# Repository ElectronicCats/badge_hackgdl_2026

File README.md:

# Badge Hack GDL 2026

El Badge Hack GDL 2026 es un dispositivo de hardware abierto diseñado para la
comunidad de hackers, desarrolladores y entusiastas de la tecnología. Integra
un procesador Linux RV1106 con cámara, LED RGB, botones y USB-C, y un firmware
propio con captura de fotos, MTP, ADB y un editor visual de overlay.

## 🚀 Características Principales

### Procesador principal

- **RV1106G3**: procesador Linux de alto rendimiento
  - ARM Cortex-A7 + MCU RISC-V
  - NPU integrada
  - ISP integrado
  - Soporte completo para Linux

### Interfaces y Conectividad

- **GPIOs**: pines de propósito general
- **MIPI CSI**: cámara SC3336 de 3 MP
- **UART**: consola serial de depuración
- **USB-C**: datos y alimentación (MTP, ADB y RNDIS)

### Periféricos Integrados

- **NeoPixel**: LED RGB WS2812E por SPI
- **Batería**: soporte para 18650 con gestión de energía
- **Buck Converter**: regulación DC-DC
- **Cámara**: SC3336, 2304×1296
- **Botones**: 5 botones `gpio-keys`

## 📦 Componentes del Proyecto

El proyecto está dividido en tres bloques:

### 1. Badge Principal (`hardware/`)

Incluye el diseño principal:

- Procesador RV1106G3
- LED NeoPixel WS2812E
- Gestión de energía y batería
- Interfaz MIPI para la cámara
- USB-C y botones

### 2. Firmware (`luckfox-pico`)

La capa de firmware vive en la rama `badge_hackgdl_2026_v2` del
repositorio [`ElectronicCats/luckfox-pico`](https://github.com/ElectronicCats/luckfox-pico).
Incluye:

- `badge_photo`: captura, AIQ/ISP, overlay, motor RGB y botones;
- `overlay_web`: editor visual y streaming MJPEG;
- `rndis_dhcp`: red USB y DHCP;
- MTP/ADB sobre FunctionFS con uMTP-Responder;
- board config, DTS, kernel fragment, MCU y overlay;
- scripts de build, flasheo y pruebas.

### 3. Add-ons (`Add-ons/`)

Diseños y firmware de los add-ons Pescadito y Tortuguita.

## 📋 Especificaciones Técnicas

| Componente | Especificación |
|---|---|
| Procesador | RV1106G3 (ARM Cortex-A7 + RISC-V MCU + NPU + ISP) |
| Sistema Operativo | Linux (BusyBox) |
| Cámara | SC3336, 2304×1296, MIPI CSI-2 |
| LED | WS2812E NeoPixel por SPI0 |
| Batería | 18650 |
| USB | USB-C: MTP + ADB + RNDIS |
| Botones | 5 `gpio-keys` |
| Almacenamiento | SPI NAND 256 MB, `/userdata` UBIFS |

## 🔌 Interfaces del RV1106

### Comunicación

- **UART**: consola serial de depuración
- **SPI**: LED WS2812 y periféricos
- **I2C**: cámara y sensores
- **USB**: MTP, ADB y RNDIS

### Multimedia e Imagen

- **MIPI CSI**: cámara SC3336
- **ISP**: procesamiento de imagen integrado
- **VENC**: JPEG y MJPEG para fotos y editor

### Control

- **GPIOs**: botones, LED y señales de la cámara
- **PWM**: disponible para periféricos

---

## **Primeros pasos**

El badge está basado en el hardware y el SDK de la Luckfox Pico Pro Max. Para
detalles de la plataforma puedes consultar la
[Wiki oficial de Luckfox](https://wiki.luckfox.com/Luckfox-Pico-Pro-Max/).

En esta sección aprenderás a:

- encender y usar tu badge;
- tomar fotografías;
- copiar las imágenes a tu computadora;
- personalizar el overlay de las fotos;
- abrir el editor web.

### **1. Alimentar tu badge**

Puedes alimentar la badge de dos maneras:

- con una batería **18650** en el compartimento trasero;
- por **USB-C** desde una computadora o cargador.

Respeta la polaridad marcada en el portapilas. El USB-C también transporta
MTP, ADB y RNDIS.

### **2. Encender el badge**

El interruptor **OFF/ON** está en el lado derecho de la placa.

1. Conecta la batería y/o el USB-C.
2. Coloca el interruptor en **ON**.
3. Espera el **doble destello verde** del NeoPixel.

El arranque es **cámara-first**: la aplicación inicia la cámara y el LED, y
sólo cuando la cámara está lista expone MTP, ADB y la web. En el arranque real
esto tarda aproximadamente **25–30 segundos**. Es normal que durante ese tiempo
la badge todavía no aparezca en la computadora.

### **3. Botones**

| Botón | `gpio-keys` | Función por defecto |
|---|---|---|
| Superior | `KEY_ENTER` | Tomar foto |
| USER1 (arriba) | `KEY_UP` | Acción de usuario programable |
| USER2 | `KEY_RIGHT` | Acción de usuario programable |
| USER3 | `KEY_LEFT` | Siguiente rutina RGB |
| USER4 (abajo) | `KEY_DOWN` | Rutina RGB anterior |

USER1 y USER2 están libres para que agregues tus propias acciones en
`badge/app/src/user_led.c`.

### **Blink Blink!**

Presiona **USER3** y **USER4** para recorrer las rutinas del NeoPixel:

1. `Off`
2. `Breath`
3. `Rainbow`
4. `Pulse`
5. `Alert`
6. `Candle`

Al arrancar, el LED hace dos destellos verdes y luego queda en `Off` hasta que
selecciones una rutina.

### **📸 Tomar fotografías**

Con la badge encendida y la cámara lista, presiona el **botón superior**.

Al capturar:

- el NeoPixel hace un destello blanco;
- la foto se guarda en `/userdata/photos`;
- el JPEG aparece por MTP en **Badge Hack GDL 2026 Photos**.

La foto final es de **2304×1296**, con giro de 180° y el overlay configurado.
El nombre usa la fecha y hora del sistema; como la badge no tiene RTC con
batería, es normal ver nombres como `IMG_19700101_000611_0000.jpg`.

### **💾 Extraer fotografías**

Las imágenes se transfieren por **MTP**. Conecta la badge por USB-C y espera a
que termine el arranque de la cámara.

**Windows**

1. Abre **Este equipo**.
2. Entra a **Badge Hack GDL 2026**.
3. Abre **Badge Hack GDL 2026 Photos**.
4. Copia los archivos `IMG_*.jpg`.
5. Usa **Quitar hardware de forma segura** antes de desconectar.

**Linux (GNOME/gvfs)**

1. Conecta la badge.
2. Abre el gestor de archivos; aparece como **Badge Hack GDL 2026**.
3. Entra a **Badge Hack GDL 2026 Photos**.

También puedes usar la terminal:

```bash
gio mount mtp://
gio list 'mtp://Electronic_Cats_Badge_Hack_GDL_2026_<serial>/Badge Hack GDL 2026 Photos'
```

**macOS:** instala **OpenMTP** o **Android File Transfer** y abre el
dispositivo. La carpeta de fotos tiene el mismo nombre.

La carpeta **Badge Config** contiene `overlay.ini`, la configuración del
overlay. Puedes copiarla, editarla en tu computadora y volver a copiarla; la
app y el editor la detectan automáticamente.

> En Windows, algunos clientes MTP no permiten editar un archivo “en sitio”.
> Si falla, copia `overlay.ini` al escritorio, edítalo y cópialo de vuelta a
> **Badge Config**. También puedes usar el editor web.

### **⚙ Archivo `overlay.ini`**

`overlay.ini` define el texto y los dos logos que se dibujan sobre la foto.
Ejemplo con los valores por defecto:

```ini
[logo1]
enabled = 1
x = 160
y = 1034
image = /oem/usr/share/badge/electroniccats.bmp

[logo2]
enabled = 1
x = 1976
y = 1024
image = /oem/usr/share/badge/hack_gdl.bmp

[text]
enabled = 1
x = 828
y = 92
text = Hack GDL 2026
size = 100
color = fff799
font = /oem/usr/share/badge/font.ttf
```

- `enabled`: `1` muestra el elemento, `0` lo oculta.
- `x`, `y`: posición en píxeles. El RGN del RV1106 exige coordenadas **pares**;
  la app y el editor las normalizan.
- `image`: ruta del BMP dentro de la imagen.
- `text`, `size`, `color`, `font`: texto, tamaño, color RGB hexadecimal y
  fuente del OSD.

Los cambios se aplican a la siguiente foto. Puedes editar el archivo por MTP o
usar el editor web; ambos escriben el mismo `overlay.ini`.

### **🖼 Editor web**

Con la badge conectada por USB, la computadora obtiene una interfaz de red USB
(RNDIS) con IP `192.168.42.2`. Abre:

```text
http://192.168.42.1/
```

El editor permite:

- arrastrar los dos logos y el texto sobre la vista de la cámara;
- cambiar texto, tamaño, color, visibilidad y posición X/Y;
- ver el stream MJPEG en vivo;
- capturar una foto con **Capturar foto**;
- editar `overlay.ini` sin botón de guardar: el autoguardado escribe el archivo;
- ver cambios hechos por MTP sin recargar la página (sincronización en ambos
  sentidos).

Si la página no abre, espera a que termine el arranque de la cámara y revisa
que el adaptador RNDIS tenga IP. Si no hay DHCP, asigna manualmente
`192.168.42.2/24`.

---

# **🚀 ¿Te interesa saber más sobre cómo se programó todo esto?**

El firmware se organiza en una capa limpia dentro de `luckfox-pico`:

- `badge/app/src/main.c`: arranque cámara-first, botones y ciclo principal;
- `badge/app/src/camera.c`: pipeline VI/VENC y captura JPEG;
- `badge/app/src/aiq.c`: carga de AIQ y calibración del ISP;
- `badge/app/src/overlay.c`: overlay RGN (logos y texto);
- `badge/app/src/led_engine.c` y `user_led.c`: motor y rutinas RGB;
- `badge/app/src/overlay_web.c`: servidor del editor y streaming;
- `badge/configs/overlay-badge-fastboot/etc/init.d/S49mtp`: gadget USB;
- `badge/scripts/`: build, flasheo y pruebas.

La documentación de build y flasheo está en el
[README de la capa](https://github.com/ElectronicCats/luckfox-pico/blob/badge_hackgdl_2026_v2/badge/README.md).

---

## 🔌 Conectarse al puerto serial (Debug Serial)

Para ver logs o depurar, conecta un adaptador USB-UART de **3.3 V** al puerto
DEBUG SERIAL. Corresponde a la UART2 del RV1106:

```text
TX del adaptador → RX del badge (GPIO1_B3)
RX del adaptador → TX del badge (GPIO1_B2)
GND → GND
```

> La señal es **3.3 V TTL**. No uses adaptadores de 5 V sin nivelador.

## ✔ Adaptadores USB–Serial compatibles

Puedes usar cualquier adaptador USB-UART de 3.3 V, por ejemplo:

- CH340 / CH341
- CP2102 / CP2104
- FT232RL
- PL2303
- CP2105
- Matek F405

## 💻 Cómo abrir la terminal serial

### 🐧 Linux

```bash
dmesg | grep tty
screen /dev/ttyUSB0 115200
# o:
sudo minicom -b 115200 -D /dev/ttyUSB0
```

Para salir de `screen`: `CTRL+A`, luego `K`.

### 🍎 macOS

```bash
ls /dev/tty.*
screen /dev/tty.usbserial-XXXX 115200
```

Para salir: `CTRL+A`, luego `K`. También puedes usar CoolTerm.

### 🪟 Windows

Usa PuTTY, TeraTerm, CoolTerm o RealTerm. En el Administrador de dispositivos
identifica el puerto COM y configura:

```text
Baudrate: 115200
Data bits: 8
Parity: None
Stop bits: 1
Flow control: None
```

---

### **Comunicación ADB**

ADB está habilitado en la imagen. Se expone después del arranque de la cámara
(~25–30 s).

1. Conecta la badge por USB-C.
2. Ejecuta:

```bash
adb devices
adb shell
```

El shell entra como **root**. ADB forma parte de las Android Platform Tools:

```text
https://developer.android.com/studio/releases/platform-tools
```

En Linux también puedes instalarlo con:

```bash
sudo apt update
sudo apt install android-tools-adb
```

---

## 🛠 Compilar el firmware

### Requisitos

- Linux x86_64 (probado en Ubuntu).
- Git, make, gcc/g++, bc, cpio, rsync, fakeroot, dtc, mkimage, python3, scons.
- ~25 GB libres para el SDK y los artefactos.
- Para flashear: `upgrade_tool` y acceso USB a la badge.

### Clonar y compilar

```bash
git clone -b badge_hackgdl_2026_v2 --single-branch \
  https://github.com/ElectronicCats/luckfox-pico.git
cd luckfox-pico
./badge/build.sh all
```

La primera compilación crea un worktree del SDK en `badge/build/luckfox-pico`,
descarga el toolchain RISC-V del HPMCU (~550 MB) y compila la imagen. Las
compilaciones siguientes reutilizan el worktree.

Si faltan `bison`, `flex`, `m4` o `python`, instálalos sin sudo:

```bash
./badge/scripts/install-host-tools.sh
```

Etapas disponibles:

```text
media, uboot, kernel, rootfs, app, pack, firmware, clean
```

Resultado:

```text
badge/out/update.img
```

El empaquetador de Rockchip incluye la hora de compilación en `update.img`, por
lo que un rebuild limpio no es byte-idéntico a la imagen de release. La imagen
validada de esta versión tiene:

```text
SHA256 21a1dc67597e43aa473b774031d7ca5f01394b59c68c1778c478361bb57895eb
```

La imagen validada se publicará en la sección **Releases** del repositorio; el
binario no se versiona en Git.

---

## 🌳 Device Tree y botones

La capa incluye el DTS `rv1106g-badge-fastboot.dts`; no necesitas editar el
árbol de Luckfox a mano. Los botones se exponen como `gpio-keys`:

| Botón | GPIO | Código Linux | Función |
|---|---|---|---|
| Superior | `GPIO1_D3` | `KEY_ENTER` | Captura |
| USER1 | `GPIO2_B1` | `KEY_UP` | Libre |
| USER2 | `GPIO2_B0` | `KEY_RIGHT` | Libre |
| USER3 | `GPIO2_A7` | `KEY_LEFT` | Siguiente rutina |
| USER4 | `GPIO2_A6` | `KEY_DOWN` | Rutina anterior |

El DTS también configura:

- cámara SC3336 en I2C4 (`0x30`) y MIPI CSI-2 de 2 lanes;
- LED WS2812 en SPI0 (`/dev/spidev0.0`);
- USB en modo `peripheral`;
- eliminación de `fbtft` y `mis5001` para evitar conflictos.

Puedes leer los eventos desde `/dev/input/eventX` en C o Python.

---

## 💡 NeoPixel y rutinas RGB

El motor está en `badge/app/src/led_engine.c`:

- no usa hilos, `sleep()` ni `malloc()`;
- llama a cada rutina cada ~20 ms;
- la rutina llena tres bytes (`R`, `G`, `B`) y regresa;
- el motor escribe el WS2812 por SPI a 2.4 MHz.

Para agregar una rutina, edita `badge/app/src/user_led.c`:

```c
static void my_routine(uint32_t elapsed_ms, uint8_t *rgb)
{
    uint8_t blink = ((elapsed_ms / 250) & 1) ? 255 : 0;

    rgb[0] = blink;      /* R */
    rgb[1] = 0;          /* G */
    rgb[2] = blink / 2;  /* B */
}

const led_pattern_t user_led_patterns[] = {
    { "USER demo", user_demo_frame },
    { "Mi rutina", my_routine },
};
```

USER3/USER4 recorren la lista; USER1/USER2 llaman a los hooks
`user_led_on_button_up()` y `user_led_on_button_right()`. No bloquees la rutina
ni escribas directamente en `/dev/spidev0.0`.

---

## 📸 Captura de fotografías

La captura la realiza `badge_photo`:

- inicia AIQ/ISP antes de abrir la cámara;
- espera un frame de warmup y reinicia el pipeline si hace falta;
- usa VENC 0 (JPEG q=90) para la foto final;
- usa VENC 1 (JPEG q=55, sin RGN) para el preview del editor;
- aplica giro de 180° y el overlay RGN;
- escribe el JPEG en `/userdata/.badge_photo_staging` y lo renombra a
  `/userdata/photos`.

El botón superior dispara la captura; el LED hace un destello blanco. La app
sigue viva si una captura falla y reintenta.

---

## 💾 MTP y configuración

`S49mtp` crea un gadget USB con:

- **MTP** por FunctionFS (`umtprd`);
- **ADB** por FunctionFS;
- **RNDIS** para la red USB.

El orden de arranque es:

```text
rcS → badge_photo → /tmp/badge_system.ready → S49mtp → MTP/ADB/RNDIS
```

MTP expone:

| Carpeta | Contenido |
|---|---|
| `Badge Hack GDL 2026 Photos` | Fotos `IMG_*.jpg` |
| `Badge Config` | `overlay.ini` |

No se expone `/userdata` completo ni el rootfs. El archivo `overlay.ini` se
publica en modo `0666` para que los clientes MTP puedan sobrescribirlo.

### Editar `overlay.ini` por MTP

1. Copia `overlay.ini` de **Badge Config** a tu computadora.
2. Edítalo con un editor de texto.
3. Cópialo de vuelta a **Badge Config**.
4. La app aplica el cambio en la siguiente foto; si el editor web está abierto,
   lo refleja sin F5.

En Windows, si el cliente MTP no permite sobrescribir en sitio, usa
copiar/editar/copiar o el editor web.

### Sincronización MTP ↔ editor

El editor consulta `/overlay.ini` cada segundo. Aplica cambios externos cuando:

- el archivo tiene las secciones `logo1`, `logo2` y `text`;
- el contenido se mantiene estable 700 ms;
- no hay un arrastre, un input enfocado o un autoguardado en curso.

En la dirección editor → MTP, el autoguardado escribe el archivo y actualiza su
referencia para evitar bucles.

---

## 🚀 Arranque del sistema

El firmware usa System V init con un `rcS` propio:

1. monta `/userdata` y `/dev/pts`;
2. inicia `badge_photo` en un bucle de supervisión;
3. espera `/tmp/badge_system.ready` (timeout de 35 s);
4. arranca `S49mtp` (MTP + ADB + RNDIS);
5. expone la web en `http://192.168.42.1/`.

Los scripts `S49mtp` y `rcS` están en
`badge/configs/overlay-badge-fastboot/`.

### Reconexión USB

Si desconectas y vuelves a conectar el USB con la badge encendida, `S49mtp`
reengancha el gadget automáticamente; no hace falta cortar la alimentación de
la batería. El watchdog registra los eventos en
`/userdata/badge/usb_watchdog.log`.

---

## 🖼️ Overlay de la imagen

El overlay de rootfs está en:

```text
badge/configs/overlay-badge-fastboot/
```

Incluye:

- `etc/init.d/S49mtp`, `etc/fstab`, `etc/inittab` y `etc/umtprd/`;
- `oem/usr/share/badge/` con `overlay.ini`, logos, fuente y `editor.html`;
- módulos USB (`u_ether.ko`, `usb_f_rndis.ko`).

El build copia este overlay a la imagen final.

---

# Cargar la imagen

Descarga la imagen validada desde la sección **Releases** del repositorio
`badge_hackgdl_2026`. Si compilaste localmente, usa `badge/out/update.img`.

## Windows

1. Descarga `upgrade_tool` desde la
   [Wiki de Luckfox](https://wiki.luckfox.com/Luckfox-Pico-Pro-Max/Flash-image).
2. Conecta la badge con **BOOT** presionado para entrar en maskrom.
3. Flashea con `upgrade_tool UF` y el archivo `.img`.

## Linux

Si compilaste localmente:

```bash
sudo ./badge/scripts/flash.sh badge/out/update.img
```

Si descargaste la imagen:

```bash
sudo upgrade_tool UF /ruta/al/archivo.img
```

Para entrar a maskrom:

1. Mantén presionado **BOOT**.
2. Pulsa y suelta **RST**.
3. Sigue sosteniendo **BOOT** ~5 s hasta que el host detecte `2207:110c` o
   `2207:350a`.
4. Suelta **BOOT**.

> Usa siempre `UF`; `DI -b` no es fiable en esta SPI NAND.

Si la badge ya está en Linux con ADB:

```bash
./badge/scripts/maskrom.sh
```

## macOS

1. Descarga `upgrade_tool` para macOS desde la Wiki de Luckfox.
2. Entra a maskrom con **BOOT+RST**.
3. Ejecuta `upgrade_tool UF` con la imagen.

---

## 📖 Documentación Adicional

- [Capa de firmware y build](https://github.com/ElectronicCats/luckfox-pico/blob/badge_hackgdl_2026_v2/badge/README.md)
- [Wiki de Luckfox Pico](https://wiki.luckfox.com/Luckfox-Pico-RV1106)
- [Datasheet RV1106](https://files.luckfox.com/wiki/Luckfox-Pico/PDF/Rockchip%20RV1106%20Datasheet%20V1.7-20231218.pdf)
- [KiCad Documentation](https://docs.kicad.org/)

## 🤝 Contribuciones

Este es un proyecto de hardware abierto. Las contribuciones son bienvenidas:

1. Haz un fork del repositorio.
2. Crea una rama para tu feature (`git checkout -b feature/AmazingFeature`).
3. Haz commit de tus cambios (`git commit -m 'Add some AmazingFeature'`).
4. Haz push a tu rama (`git push origin feature/AmazingFeature`).
5. Abre un Pull Request.

## 📝 Licencia

Este proyecto es de hardware abierto. Consulta los archivos de licencia para
más detalles.

## 🏢 Electronic Cats

Desarrollado con ❤️ por [Electronic Cats](https://www.electroniccats.com/).

Electronic Cats invierte tiempo y recursos en proporcionar este diseño de
hardware abierto. Por favor, apoya a Electronic Cats y al hardware abierto
comprando productos de Electronic Cats.

## 📞 Contacto y soporte

- **Website**: [https://www.electroniccats.com/](https://www.electroniccats.com/)
- **GitHub**: [ElectronicCats](https://github.com/ElectronicCats)
- **Issues**: usa la sección de Issues del repositorio.

## 🙏 Agradecimientos

Gracias a toda la comunidad de hardware abierto y a todas las personas que
hacen posibles proyectos como este.

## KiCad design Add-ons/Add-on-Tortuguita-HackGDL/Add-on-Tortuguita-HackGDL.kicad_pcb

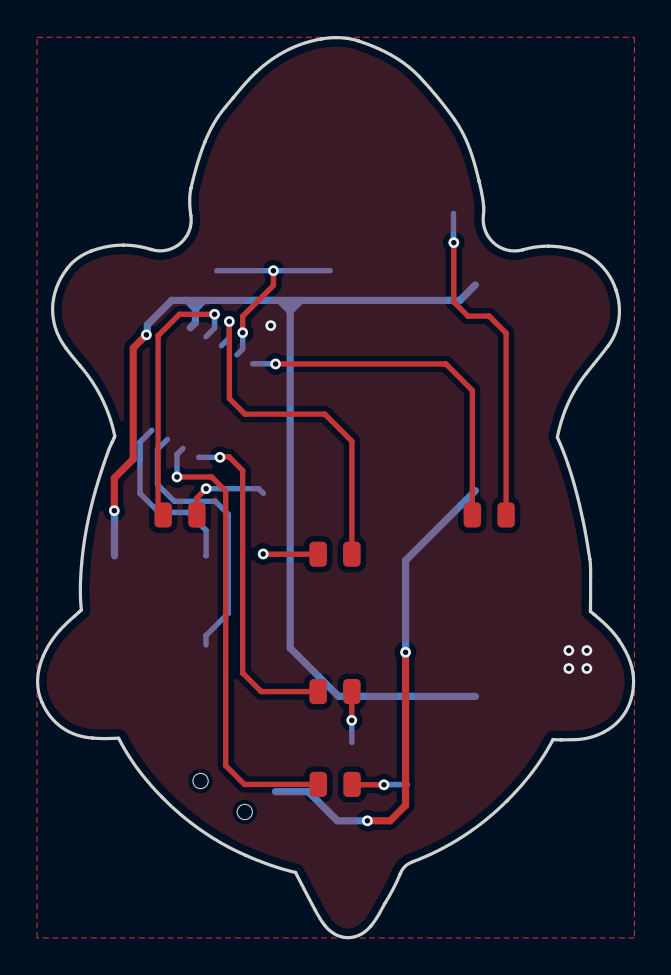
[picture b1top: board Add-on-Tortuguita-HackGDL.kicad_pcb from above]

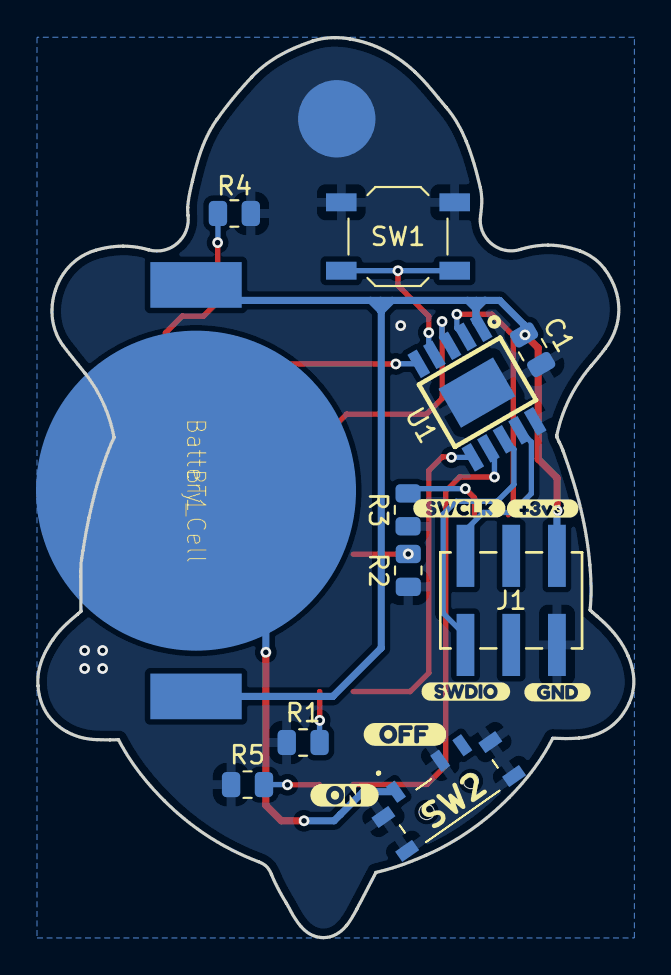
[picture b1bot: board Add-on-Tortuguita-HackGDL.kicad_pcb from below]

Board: 2 copper layers, 33.1 x 50.0 mm, 22 parts (17 on the bottom side), 16 nets.

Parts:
BT1: Battery_Cell; BAT-HLD-001
C1: 0.1uF; C_0805_2012Metric
D1, D2, D3, D4, D5: Red; LED_0805_2012Metric
J1: Conn_02x03_Odd_Even; B-2100N06P-B111_CKM
R1, R2, R3, R4, R5: 330R; R_0805_2012Metric
SW1: SW_RST; SW_SPST_TL3342
SW2: On; MSK12C02
U1: PY32F002AA15M6TU; PY32F002AA15M
kibuzzard-684B03BD: G***; kibuzzard-684B03BD
kibuzzard-684B03C9: G***; kibuzzard-684B03C9
kibuzzard-697CCF2B: G***; kibuzzard-697CCF2B
kibuzzard-6892952E: G***; kibuzzard-6892952E
kibuzzard-68929515: G***; kibuzzard-68929515
kibuzzard-68929520: G***; kibuzzard-68929520

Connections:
+3.3V: BT1.2 (+), C1.1, J1.6, U1.1 (VCC)
/NRST: SW1.2, U1.4 (PA0/PF2-NRST)
/PA1: D4.2 (A), U1.5 (PA1)
/PA5: D2.2 (A), U1.3 (PA5/PF1-OSCOUT)
/PA6: D1.2 (A), U1.6 (PA6)
/PA7: D5.2 (A), U1.7 (PA7)
/PF0: D3.2 (A), U1.2 (PF0-OSCIN)
/SWCLK: J1.2, U1.9 (PA14-SWC/PB3)
/SWDIO: J1.1, U1.8 (PA13-SWD)
GND: C1.2, J1.5, R1.1, R2.1, R3.1, R4.1, R5.1, SW1.1, SW2.2 (A), SW2.4 (C), U1.10 (GND)
unnamed: BT1.1 (-), SW2.1 (B)
unnamed: D1.1 (K), R1.2
unnamed: D2.1 (K), R2.2
unnamed: D3.1 (K), R3.2
unnamed: D4.1 (K), R4.2
unnamed: D5.1 (K), R5.2

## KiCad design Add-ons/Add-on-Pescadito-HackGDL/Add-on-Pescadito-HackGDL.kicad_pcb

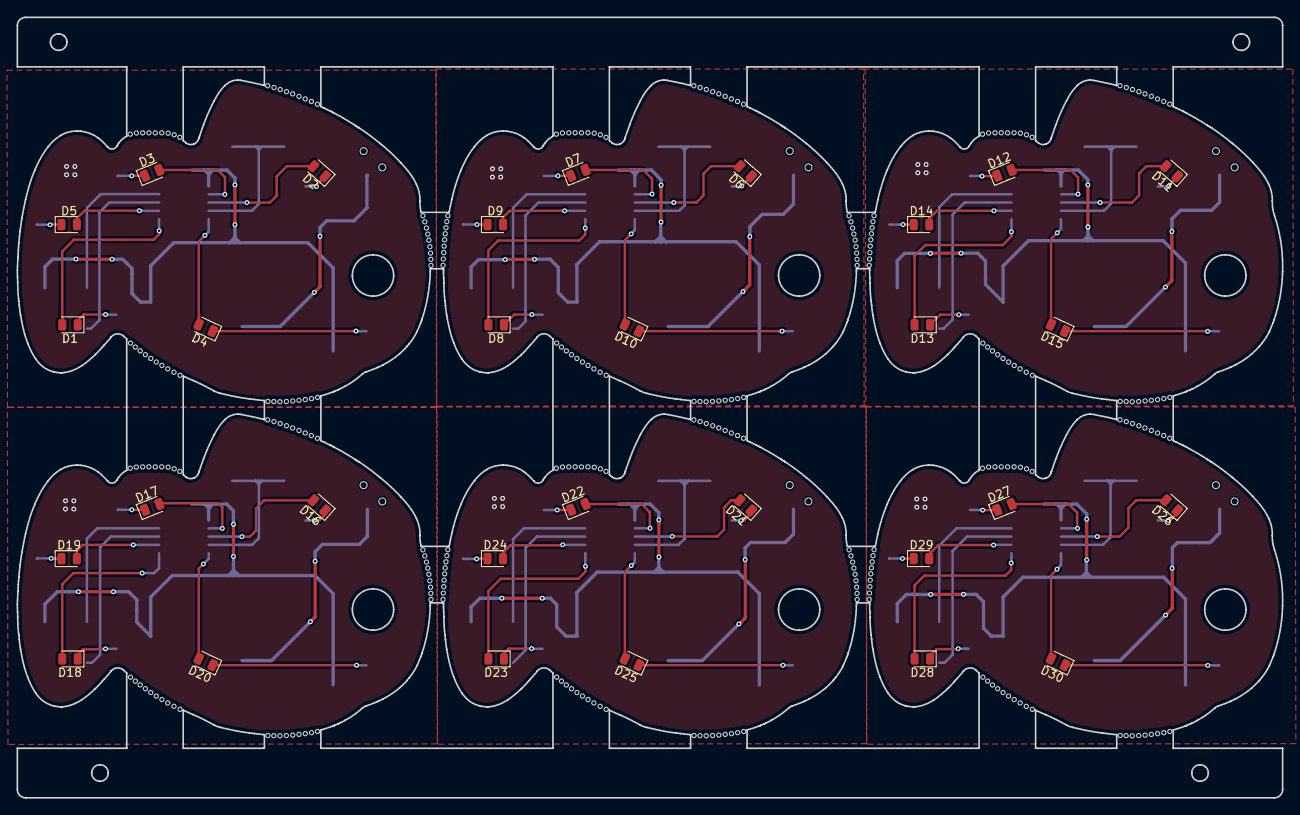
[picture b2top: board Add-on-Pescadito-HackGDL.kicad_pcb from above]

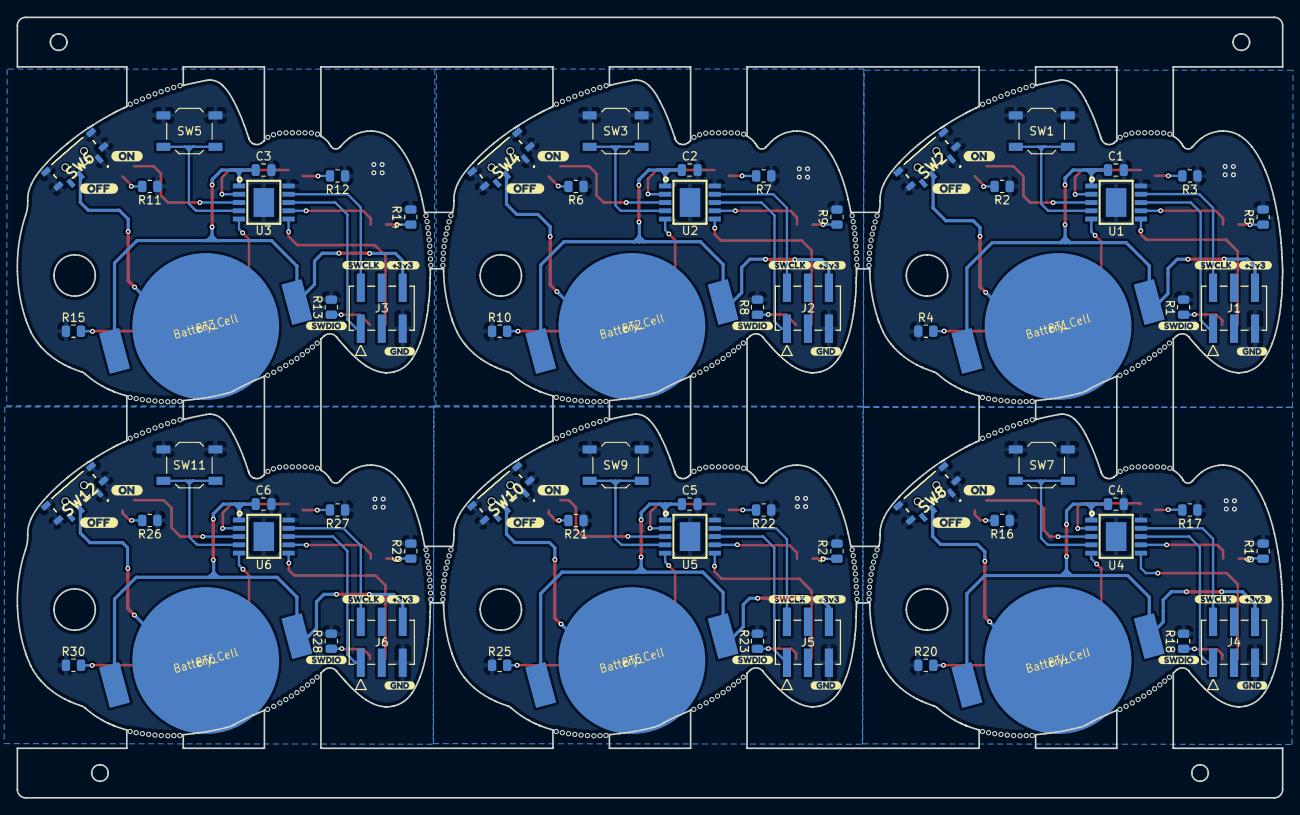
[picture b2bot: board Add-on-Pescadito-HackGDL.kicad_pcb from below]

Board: 2 copper layers, 153.2 x 94.5 mm, 132 parts (102 on the bottom side), 96 nets.

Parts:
BT1, BT2, BT3, BT4, BT5, BT6: Battery_Cell; BAT-HLD-001
C1, C2, C3, C4, C5, C6: 0.1uF; C_0805_2012Metric
D1, D3, D4, D5: Red; LED_0805_2012Metric
D2, D6, D11, D16, D21, D26: White; LED_0805_2012Metric
D7, D8, D9, D10: Pink; LED_0805_2012Metric
D12, D13, D14, D15: Blue; LED_0805_2012Metric
D17, D18, D19, D20: Yellow; LED_0805_2012Metric
D22, D23, D24, D25: Green; LED_0805_2012Metric
D27, D28, D29, D30: Orange; LED_0805_2012Metric
J1, J2, J3, J4, J5, J6: Conn_02x03_Odd_Even; B-2100N06P-B111_CKM
R1, R2, R3, R4, R5, R6, R7, R8, R9, R10, R11, R12, R13, R14, R15, R16, R17, R18, R19, R20, R21, R22, R23, R24, R25, R26, R27, R28, R29, R30: 330R; R_0805_2012Metric
SW1, SW3, SW5, SW7, SW9, SW11: SW_RST; SW_SPST_TL3342
SW2, SW4, SW6, SW8, SW10, SW12: On; MSK12C02
U1, U2, U3, U4, U5, U6: PY32F002AA15M6TU; PY32F002AA15M
kibuzzard-684B03BD, kibuzzard-684B03BD#2, kibuzzard-684B03BD#3, kibuzzard-684B03BD#4, kibuzzard-684B03BD#5, kibuzzard-684B03BD#6: G***; kibuzzard-684B03BD
kibuzzard-684B03C9, kibuzzard-684B03C9#2, kibuzzard-684B03C9#3, kibuzzard-684B03C9#4, kibuzzard-684B03C9#5, kibuzzard-684B03C9#6: G***; kibuzzard-684B03C9
kibuzzard-697CCF2B, kibuzzard-697CCF2B#2, kibuzzard-697CCF2B#3, kibuzzard-697CCF2B#4, kibuzzard-697CCF2B#5, kibuzzard-697CCF2B#6: G***; kibuzzard-697CCF2B
kibuzzard-6892952E, kibuzzard-6892952E#2, kibuzzard-6892952E#3, kibuzzard-6892952E#4, kibuzzard-6892952E#5, kibuzzard-6892952E#6: G***; kibuzzard-6892952E
kibuzzard-68929515, kibuzzard-68929515#2, kibuzzard-68929515#3, kibuzzard-68929515#4, kibuzzard-68929515#5, kibuzzard-68929515#6: G***; kibuzzard-68929515
kibuzzard-68929520, kibuzzard-68929520#2, kibuzzard-68929520#3, kibuzzard-68929520#4, kibuzzard-68929520#5, kibuzzard-68929520#6: G***; kibuzzard-68929520

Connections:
/Blue_Fish/+3.3V: BT3.2 (+), C3.1, J3.6, U3.1 (VCC)
/Blue_Fish/GND: C3.2, J3.5, R11.1, R12.1, R13.1, R14.1, R15.1, SW5.1, SW6.1 (A), SW6.4 (C), U3.10 (GND)
/Blue_Fish/NRST: SW5.2, U3.4 (PA0/PF2-NRST)
/Blue_Fish/PA1: D15.2 (A), U3.5 (PA1)
/Blue_Fish/PA5: D11.2 (A), U3.3 (PA5/PF1-OSCOUT)
/Blue_Fish/PA6: D13.2 (A), U3.6 (PA6)
/Blue_Fish/PA7: D14.2 (A), U3.7 (PA7)
/Blue_Fish/PF0: D12.2 (A), U3.2 (PF0-OSCIN)
/Blue_Fish/SWCLK: J3.2, U3.9 (PA14-SWC/PB3)
/Blue_Fish/SWDIO: J3.1, U3.8 (PA13-SWD)
/Green_Fish/+3.3V: BT5.2 (+), C5.1, J5.6, U5.1 (VCC)
/Green_Fish/GND: C5.2, J5.5, R21.1, R22.1, R23.1, R24.1, R25.1, SW9.1, SW10.1 (A), SW10.4 (C), U5.10 (GND)
/Green_Fish/NRST: SW9.2, U5.4 (PA0/PF2-NRST)
/Green_Fish/PA1: D25.2 (A), U5.5 (PA1)
/Green_Fish/PA5: D21.2 (A), U5.3 (PA5/PF1-OSCOUT)
/Green_Fish/PA6: D23.2 (A), U5.6 (PA6)
/Green_Fish/PA7: D24.2 (A), U5.7 (PA7)
/Green_Fish/PF0: D22.2 (A), U5.2 (PF0-OSCIN)
/Green_Fish/SWCLK: J5.2, U5.9 (PA14-SWC/PB3)
/Green_Fish/SWDIO: J5.1, U5.8 (PA13-SWD)
/Orange_Fish/+3.3V: BT6.2 (+), C6.1, J6.6, U6.1 (VCC)
/Orange_Fish/GND: C6.2, J6.5, R26.1, R27.1, R28.1, R29.1, R30.1, SW11.1, SW12.1 (A), SW12.4 (C), U6.10 (GND)
/Orange_Fish/NRST: SW11.2, U6.4 (PA0/PF2-NRST)
/Orange_Fish/PA1: D30.2 (A), U6.5 (PA1)
/Orange_Fish/PA5: D26.2 (A), U6.3 (PA5/PF1-OSCOUT)
/Orange_Fish/PA6: D28.2 (A), U6.6 (PA6)
/Orange_Fish/PA7: D29.2 (A), U6.7 (PA7)
/Orange_Fish/PF0: D27.2 (A), U6.2 (PF0-OSCIN)
/Orange_Fish/SWCLK: J6.2, U6.9 (PA14-SWC/PB3)
/Orange_Fish/SWDIO: J6.1, U6.8 (PA13-SWD)
/Pink_Fish/+3.3V: BT2.2 (+), C2.1, J2.6, U2.1 (VCC)
/Pink_Fish/GND: C2.2, J2.5, R6.1, R7.1, R8.1, R9.1, R10.1, SW3.1, SW4.1 (A), SW4.4 (C), U2.10 (GND)
/Pink_Fish/NRST: SW3.2, U2.4 (PA0/PF2-NRST)
/Pink_Fish/PA1: D10.2 (A), U2.5 (PA1)
/Pink_Fish/PA5: D6.2 (A), U2.3 (PA5/PF1-OSCOUT)
/Pink_Fish/PA6: D8.2 (A), U2.6 (PA6)
/Pink_Fish/PA7: D9.2 (A), U2.7 (PA7)
/Pink_Fish/PF0: D7.2 (A), U2.2 (PF0-OSCIN)
/Pink_Fish/SWCLK: J2.2, U2.9 (PA14-SWC/PB3)
/Pink_Fish/SWDIO: J2.1, U2.8 (PA13-SWD)
/Red_Fish/+3.3V: BT1.2 (+), C1.1, J1.6, U1.1 (VCC)
/Red_Fish/GND: C1.2, J1.5, R1.1, R2.1, R3.1, R4.1, R5.1, SW1.1, SW2.1 (A), SW2.4 (C), U1.10 (GND)
/Red_Fish/NRST: SW1.2, U1.4 (PA0/PF2-NRST)
/Red_Fish/PA1: D4.2 (A), U1.5 (PA1)
/Red_Fish/PA5: D2.2 (A), U1.3 (PA5/PF1-OSCOUT)
/Red_Fish/PA6: D1.2 (A), U1.6 (PA6)
/Red_Fish/PA7: D5.2 (A), U1.7 (PA7)
/Red_Fish/PF0: D3.2 (A), U1.2 (PF0-OSCIN)
/Red_Fish/SWCLK: J1.2, U1.9 (PA14-SWC/PB3)
/Red_Fish/SWDIO: J1.1, U1.8 (PA13-SWD)
/Yellow_Fish/+3.3V: BT4.2 (+), C4.1, J4.6, U4.1 (VCC)
/Yellow_Fish/GND: C4.2, J4.5, R16.1, R17.1, R18.1, R19.1, R20.1, SW7.1, SW8.1 (A), SW8.4 (C), U4.10 (GND)
/Yellow_Fish/NRST: SW7.2, U4.4 (PA0/PF2-NRST)
/Yellow_Fish/PA1: D20.2 (A), U4.5 (PA1)
/Yellow_Fish/PA5: D16.2 (A), U4.3 (PA5/PF1-OSCOUT)
/Yellow_Fish/PA6: D18.2 (A), U4.6 (PA6)
/Yellow_Fish/PA7: D19.2 (A), U4.7 (PA7)
/Yellow_Fish/PF0: D17.2 (A), U4.2 (PF0-OSCIN)
/Yellow_Fish/SWCLK: J4.2, U4.9 (PA14-SWC/PB3)
/Yellow_Fish/SWDIO: J4.1, U4.8 (PA13-SWD)
unnamed: BT1.1 (-), SW2.2 (B)
unnamed: BT2.1 (-), SW4.2 (B)
unnamed: BT3.1 (-), SW6.2 (B)
unnamed: BT4.1 (-), SW8.2 (B)
unnamed: BT5.1 (-), SW10.2 (B)
unnamed: BT6.1 (-), SW12.2 (B)
unnamed: D1.1 (K), R1.2
unnamed: D2.1 (K), R2.2
unnamed: D3.1 (K), R3.2
unnamed: D4.1 (K), R4.2
unnamed: D5.1 (K), R5.2
unnamed: D6.1 (K), R6.2
unnamed: D7.1 (K), R7.2
unnamed: D8.1 (K), R8.2
unnamed: D9.1 (K), R9.2
unnamed: D10.1 (K), R10.2
unnamed: D11.1 (K), R11.2
unnamed: D12.1 (K), R12.2
unnamed: D13.1 (K), R13.2
unnamed: D14.1 (K), R14.2
unnamed: D15.1 (K), R15.2
unnamed: D16.1 (K), R16.2
unnamed: D17.1 (K), R17.2
unnamed: D18.1 (K), R18.2
unnamed: D19.1 (K), R19.2
unnamed: D20.1 (K), R20.2
unnamed: D21.1 (K), R21.2
unnamed: D22.1 (K), R22.2
unnamed: D23.1 (K), R23.2
unnamed: D24.1 (K), R24.2
unnamed: D25.1 (K), R25.2
unnamed: D26.1 (K), R26.2
unnamed: D27.1 (K), R27.2
unnamed: D28.1 (K), R28.2
unnamed: D29.1 (K), R29.2
unnamed: D30.1 (K), R30.2

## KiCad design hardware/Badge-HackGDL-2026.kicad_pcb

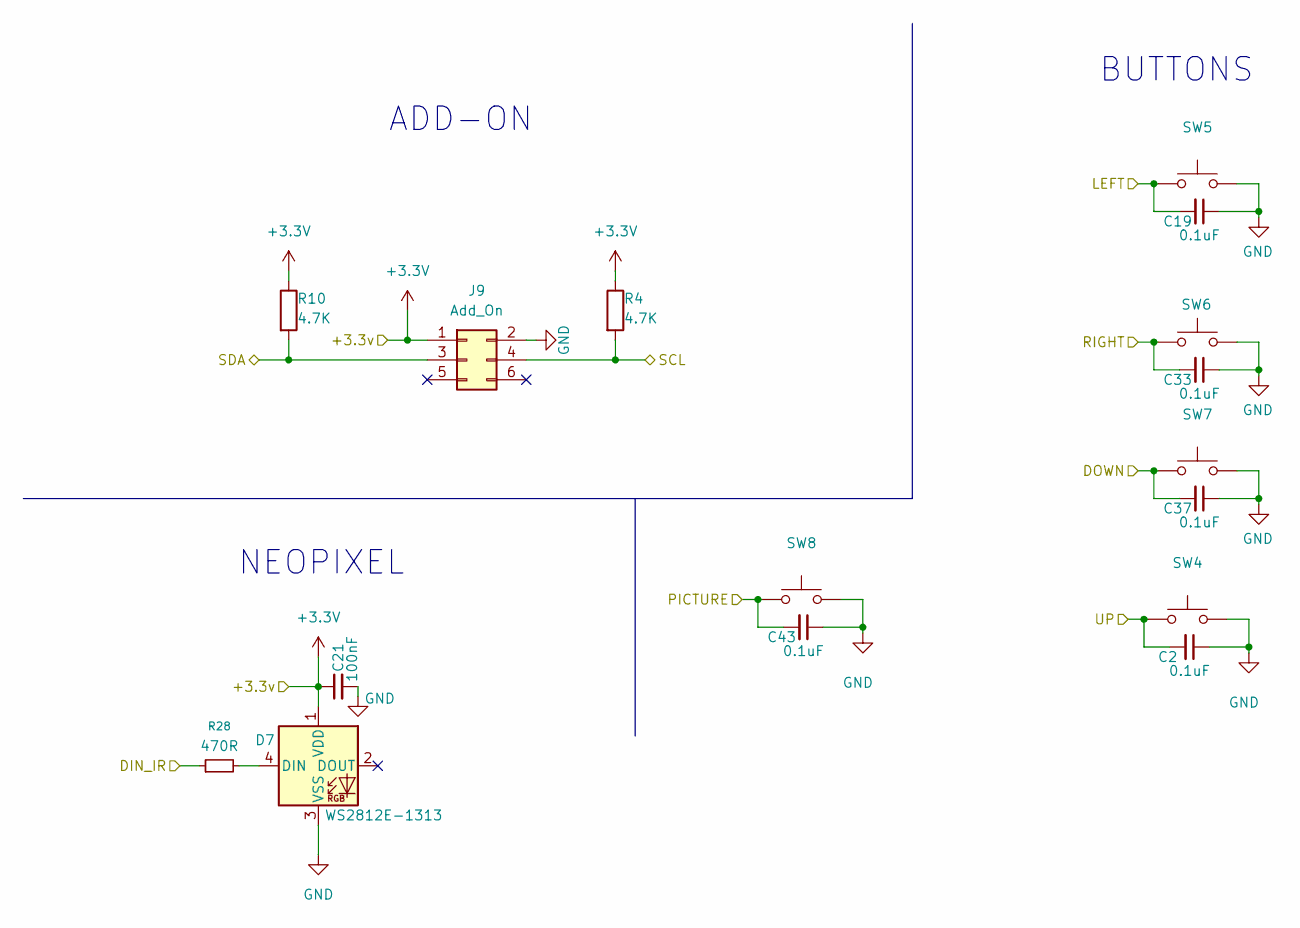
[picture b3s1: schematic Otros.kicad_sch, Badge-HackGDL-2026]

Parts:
C2, C19, C33, C37, C43: 0.1uF; C_0603_1608Metric; LCSC# C478888
C21: 100nF; C_0402_1005Metric; LCSC# C77020
D7: WS2812E-1313; LCSC# C5446700
J9: Add_On; PinSocket_2x03_P2.54mm_Vertical; LCSC# C5116527
R4, R10: 4.7K; C_0603_1608Metric; LCSC# C2907166
R28: 470R; R_0603_1608Metric; LCSC# C23179
SW4, SW5, SW6, SW7: SW_SPST_TL3342; LCSC# C318889
SW8: Button_6.6x6.5; LCSC# C480263

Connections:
+3.3V: C21.1, D7.1 (VDD), J9.1, R4.1, R10.1; also elsewhere on the board
/MCU/DIN_IR: R28.1; also elsewhere on the board
/MCU/DOWN: C37.2, SW7.2; also elsewhere on the board
/MCU/LEFT: C19.2, SW5.2; also elsewhere on the board
/MCU/PICTURE: C43.2, SW8.2; also elsewhere on the board
/MCU/RIGHT: C33.2, SW6.2; also elsewhere on the board
/MCU/SCL: J9.4, R4.2; also elsewhere on the board
/MCU/SDA: J9.3, R10.2; also elsewhere on the board
/MCU/UP: C2.2, SW4.2; also elsewhere on the board
GND: C2.1, C19.1, C21.2, C33.1, C37.1, C43.1, D7.3 (VSS), J9.2, SW4.1, SW5.1, SW6.1, SW7.1, SW8.1; also elsewhere on the board
unnamed: D7.4 (DIN), R28.2

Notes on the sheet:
BUTTONS
ADD-ON
NEOPIXEL

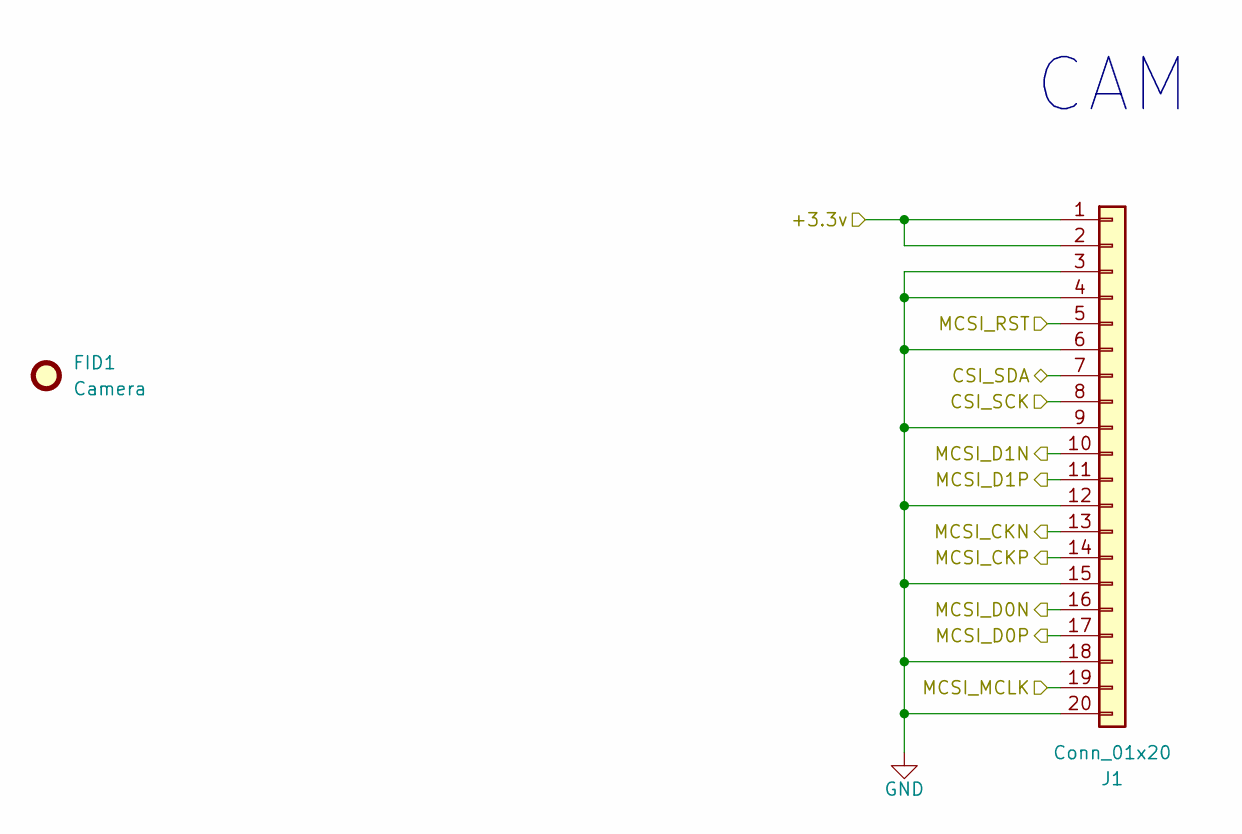
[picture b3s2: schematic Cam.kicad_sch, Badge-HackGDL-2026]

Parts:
FID1: Camera; Untitled
J1: Conn_01x20; Hirose_FH12-20S-0.5SH_1x20-1MP_P0.50mm_Horizontal; LCSC# C2906119

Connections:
+3.3V: J1.1, J1.2; also elsewhere on the board
/Cam/CSI_SCK: J1.8; also elsewhere on the board
/Cam/CSI_SDA: J1.7; also elsewhere on the board
/Cam/MCSI_CKN: J1.13; also elsewhere on the board
/Cam/MCSI_CKP: J1.14; also elsewhere on the board
/Cam/MCSI_D0N: J1.16; also elsewhere on the board
/Cam/MCSI_D0P: J1.17; also elsewhere on the board
/Cam/MCSI_D1N: J1.10; also elsewhere on the board
/Cam/MCSI_D1P: J1.11; also elsewhere on the board
/Cam/MCSI_MCLK: J1.19; also elsewhere on the board
/Cam/MCSI_RST: J1.5; also elsewhere on the board
GND: J1.3, J1.4, J1.6, J1.9, J1.12, J1.15, J1.18, J1.20; also elsewhere on the board

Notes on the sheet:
CAM

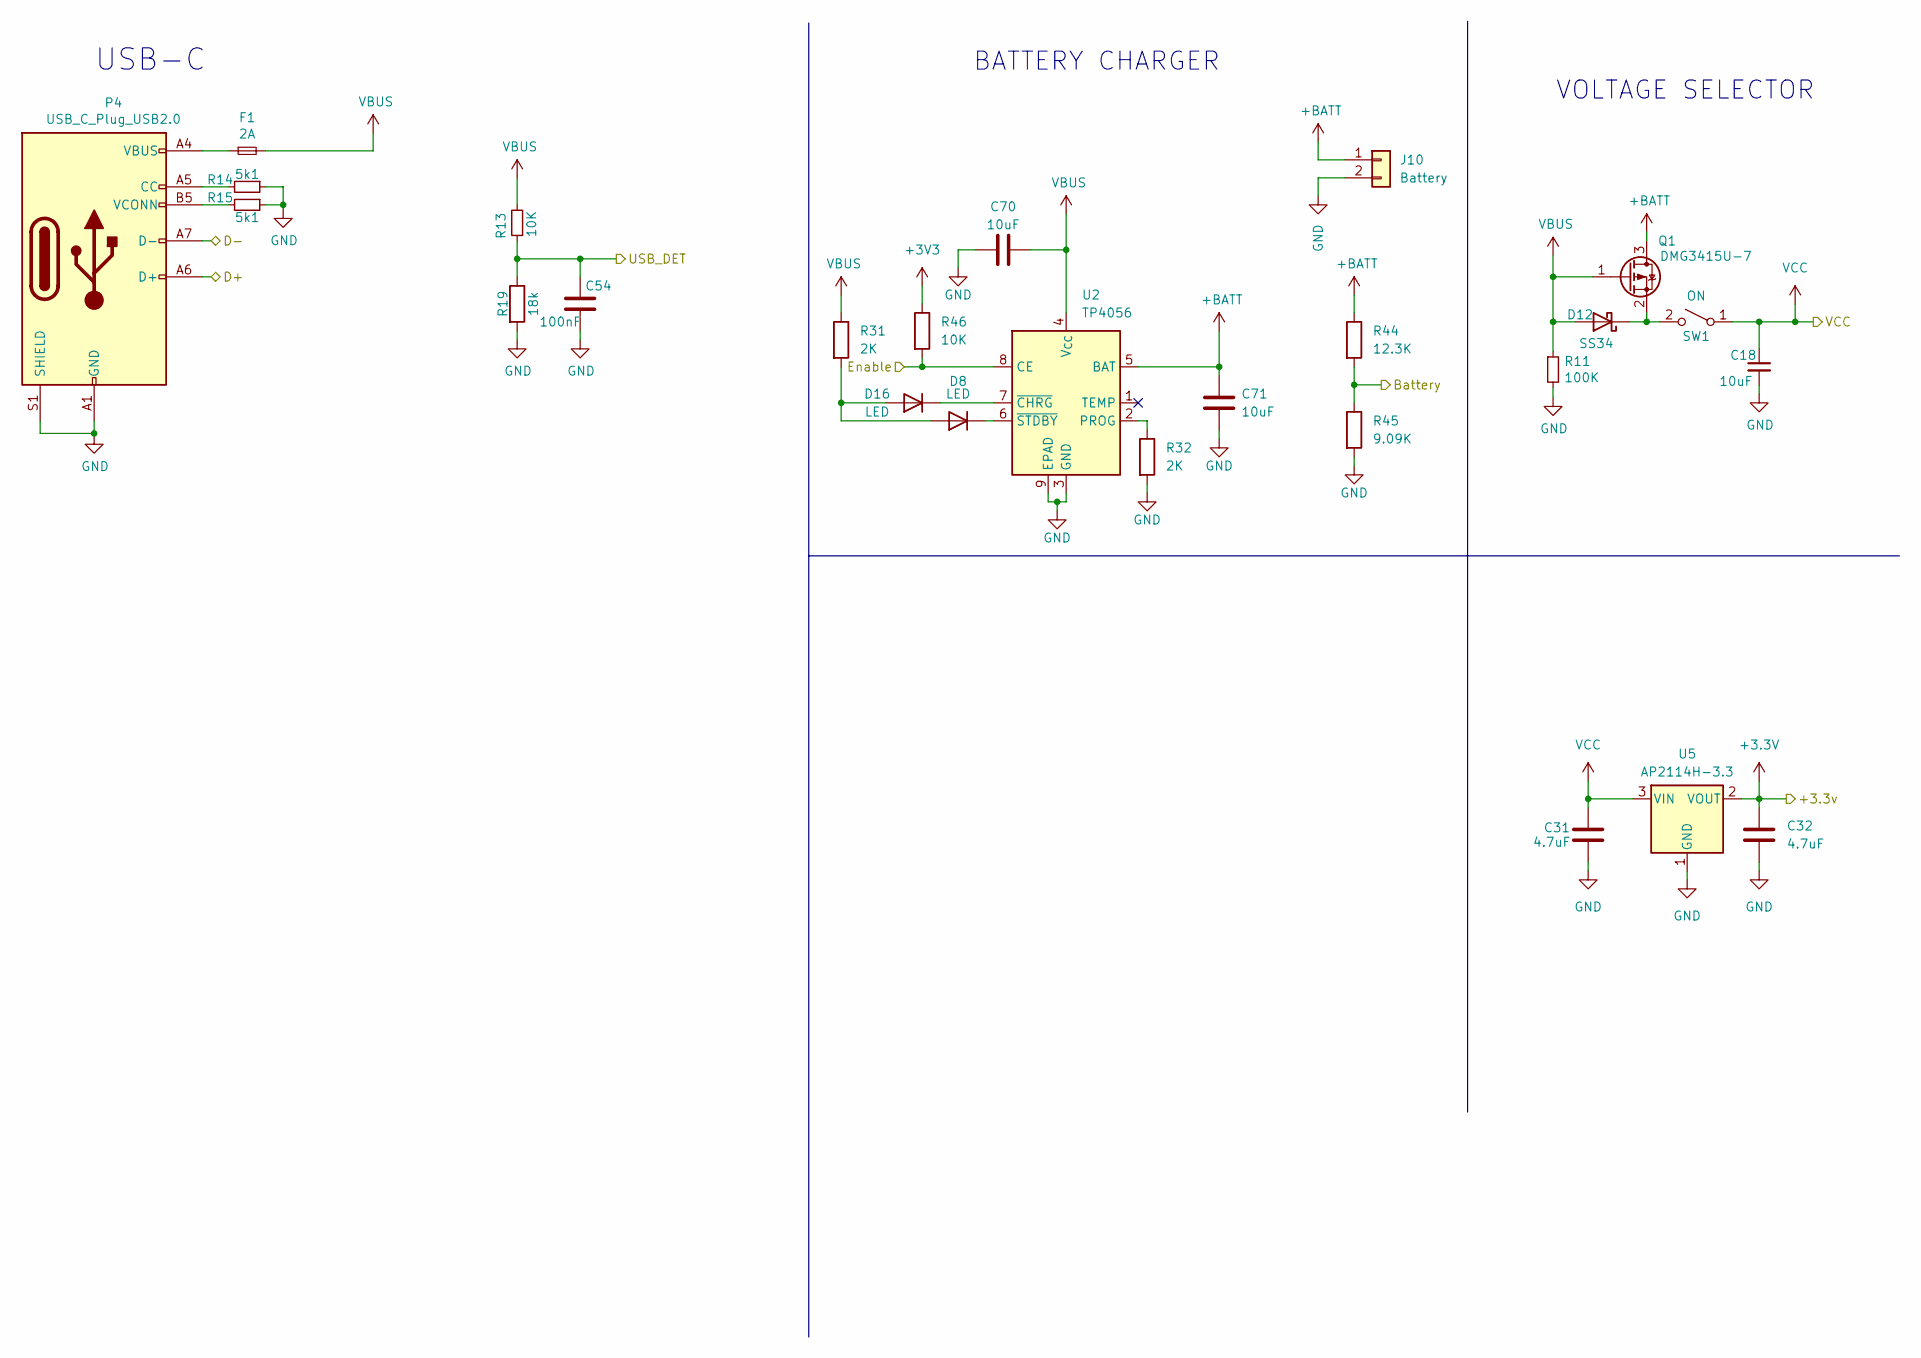
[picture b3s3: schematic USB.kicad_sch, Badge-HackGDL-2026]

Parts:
C18: 10uF; C_0402_1005Metric; LCSC# C7472949
C31, C32: 4.7uF; C_0402_1005Metric; LCSC# C368809
C54: 100nF; C_0402_1005Metric; LCSC# C77020
C70, C71: 10uF; C_0603_1608Metric; LCSC# C96446
D8, D16: LED; LED_0603_1608Metric; LCSC# C22371297
D12: SS34; D_SMA; LCSC# C908680
F1: 2A; Fuse_0603_1608Metric; LCSC# C41380229
J10: Battery; BatteryHolder_Keystone_1042_1x18650; LCSC# C2988620
P4: USB_C_Plug_USB2.0; C393939; LCSC# C2760486
Q1: DMG3415U-7; SOT-23; LCSC# C96616
R11: 100K; R_0603_1608Metric; LCSC# C15458
R13, R46: 10K; R_0402_1005Metric; LCSC# C2759535
R14, R15: 5k1; R_0603_1608Metric; LCSC# C2907044
R19: 18k; R_0402_1005Metric; LCSC# C323741
R31, R32: 2K; R_0603_1608Metric; LCSC# C2907022
R44: 12.3K; R_0402_1005Metric; LCSC# C346621
R45: 9.09K; R_0402_1005Metric; LCSC# C852966
SW1: ON; SW_Slide_SPDT_Angled_CK_OS102011MA1Q; LCSC# C393937
U2: TP4056; SOIC-8-1EP_3.9x4.9mm_P1.27mm_EP2.41x3.3mm_ThermalVias; LCSC# C725790
U5: AP2114H-3.3; SOT-223-3_TabPin2; LCSC# C150716

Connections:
+3.3V: C32.1, U5.2 (VOUT); also elsewhere on the board
+3V3: R46.1; also elsewhere on the board
+BATT: C71.1, J10.1, Q1.3 (D), R44.1, U2.5 (BAT)
/MCU/Battery: R44.2, R45.1; also elsewhere on the board
/MCU/D+: P4.A6 (D+); also elsewhere on the board
/MCU/D-: P4.A7 (D-); also elsewhere on the board
/MCU/Enable: R46.2, U2.8 (CE); also elsewhere on the board
/MCU/USB_DET: C54.1, R13.1, R19.1; also elsewhere on the board
GND: C18.2, C31.2, C32.2, C54.2, C70.1, C71.2, J10.2, P4.A1 (GND), P4.A12 (GND), P4.B1 (GND), P4.B12 (GND), P4.S1 (SHIELD), R11.2, R14.1, R15.1, R19.2, R32.2, R45.2, U2.3 (GND), U2.9 (EPAD), U5.1 (GND); also elsewhere on the board
unnamed: D8.1 (K), U2.6 (~STDBY)
unnamed: D12.1 (K), Q1.2 (S), SW1.2 (B)
unnamed: D8.2 (A), D16.2 (A), R31.2
unnamed: D16.1 (K), U2.7 (~CHRG)
unnamed: F1.1, P4.A4 (VBUS), P4.A9 (VBUS), P4.B4 (VBUS), P4.B9 (VBUS)
unnamed: P4.A5 (CC), R14.2
unnamed: P4.B5 (VCONN), R15.2
unnamed: R32.1, U2.2 (PROG)
VBUS: C70.2, D12.2 (A), F1.2, Q1.1 (G), R11.1, R13.2, R31.1, U2.4 (V_{CC})
VCC: C18.1, C31.1, SW1.1 (A), U5.3 (VIN); also elsewhere on the board

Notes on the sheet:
VOLTAGE SELECTOR
USB-C
BATTERY CHARGER
